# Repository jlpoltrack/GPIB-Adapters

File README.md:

# GPIB-Adapters

GPIB (IEEE-488) adapters that plug straight into an instrument's GPIB socket.

| Folder | What it is |
|---|---|
| [gpib-core](gpib-core) | Shared, board-independent firmware (descended from xyphro's UsbGpib) |
| [LANGPIB-WCH](LANGPIB-WCH) | GPIB to Ethernet/USB on the WCH CH32V407 (on-chip PHY), USB-powered |
| [USBGPIB-STM32](USBGPIB-STM32) | USB to GPIB on an STM32F1: USBTMC and Prologix-compatible serial |

## Build

Clone with `git clone --recurse-submodules`. Each board's firmware builds against `../../gpib-core`.

```
make -C gpib-core test             # host tests
make -C USBGPIB-STM32/Firmware     # arm-none-eabi-gcc
make -C LANGPIB-WCH/Firmware       # riscv-none-elf-gcc (xPack)
```

Flashing and setup are in each board's README and `docs/firmware.md`.

## License

[MIT](LICENSE)

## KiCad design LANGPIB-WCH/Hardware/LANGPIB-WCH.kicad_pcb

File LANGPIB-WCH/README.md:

# LANGPIB-WCH

GPIB-to-Ethernet/USB adapter that plugs onto an instrument's GPIB socket: WCH CH32V407RET6 (on-chip 10/100 PHY), HanRun
HR911105A MagJack (JLC-fitted), USB-C (bus-powered), 4 layers, 57.15 x 46.2 mm, KiCad 10.

`Hardware/` holds the design (schematic PDF, board, renders), `Firmware/` the firmware ([docs/firmware.md](docs/firmware.md)),
`docs/plan.md` the design decisions, `docs/handoff.md` the current state. The schematic, placement and routing are generated by kicad-tools `projects/langpib-wch/`.

**Status (2026-11-21):** 5 assembled boards from JLC ($50.28). Board 1 is brought up and runs an HP 3456A and an HP
66332A over USB (USBTMC, Prologix) and Ethernet (VXI-11, raw SCPI 5025, Prologix 1234, web page); what is still
unverified is listed in [docs/firmware.md](docs/firmware.md) "Still to verify".

## Hardware notes

- **RJ45 (J2):** HanRun HR911105A with magnetics, Bob Smith termination and LEDs inside, through-hole, fitted by JLC.
  MDI pairs are swapped for routing: keep the PHY's Auto-MDIX on.
- **PoE:** use an isolated 802.3af splitter with a USB-C plug, e.g. Adafruit 4552 ([docs/poe.md](docs/poe.md)).
- **GPIB plug (J3) and debug header (J4)** are hand-soldered. J4 (1x7, 2.54 mm): GND, SWIO, SWCLK, NRST, RX, TX, GND,
  the RP2350-Zero probe's order.
- **DFU:** hold SW1 (top left) while plugging in USB for the bootloader (the LQFP-64 has no BOOT pins).
- **Enclosure:** `Enclosure/` (cad-tools `projects/LANGPIB-WCH/`): two snap halves, GPIB plug screws in the bottom; button
  through a flex tab in the lid, status LED through a window in the left wall.
- **Firmware pin map:** DIO1-8 on PB13 / PB15 / PB10 / PB9 / PB12 / PB14 / PB11 / PB8 (one GPIOB read and a 256-entry
  table), REN PA15, EOI PC10, DAV PC11, NRFD PC12, NDAC PD2, IFC PB3, SRQ PB4, ATN PB5 (all 5 V tolerant), DFU PD8,
  status LED PA8, PHY LEDs PD14 (green) / PD15 (yellow) (`AFIO_PCFR1.ETHPHY_LED_RM`), USB PA11 / PA12, SDI PA13 / PA14,
  USART1 PA9 / PA10.

## License

[MIT](../LICENSE)

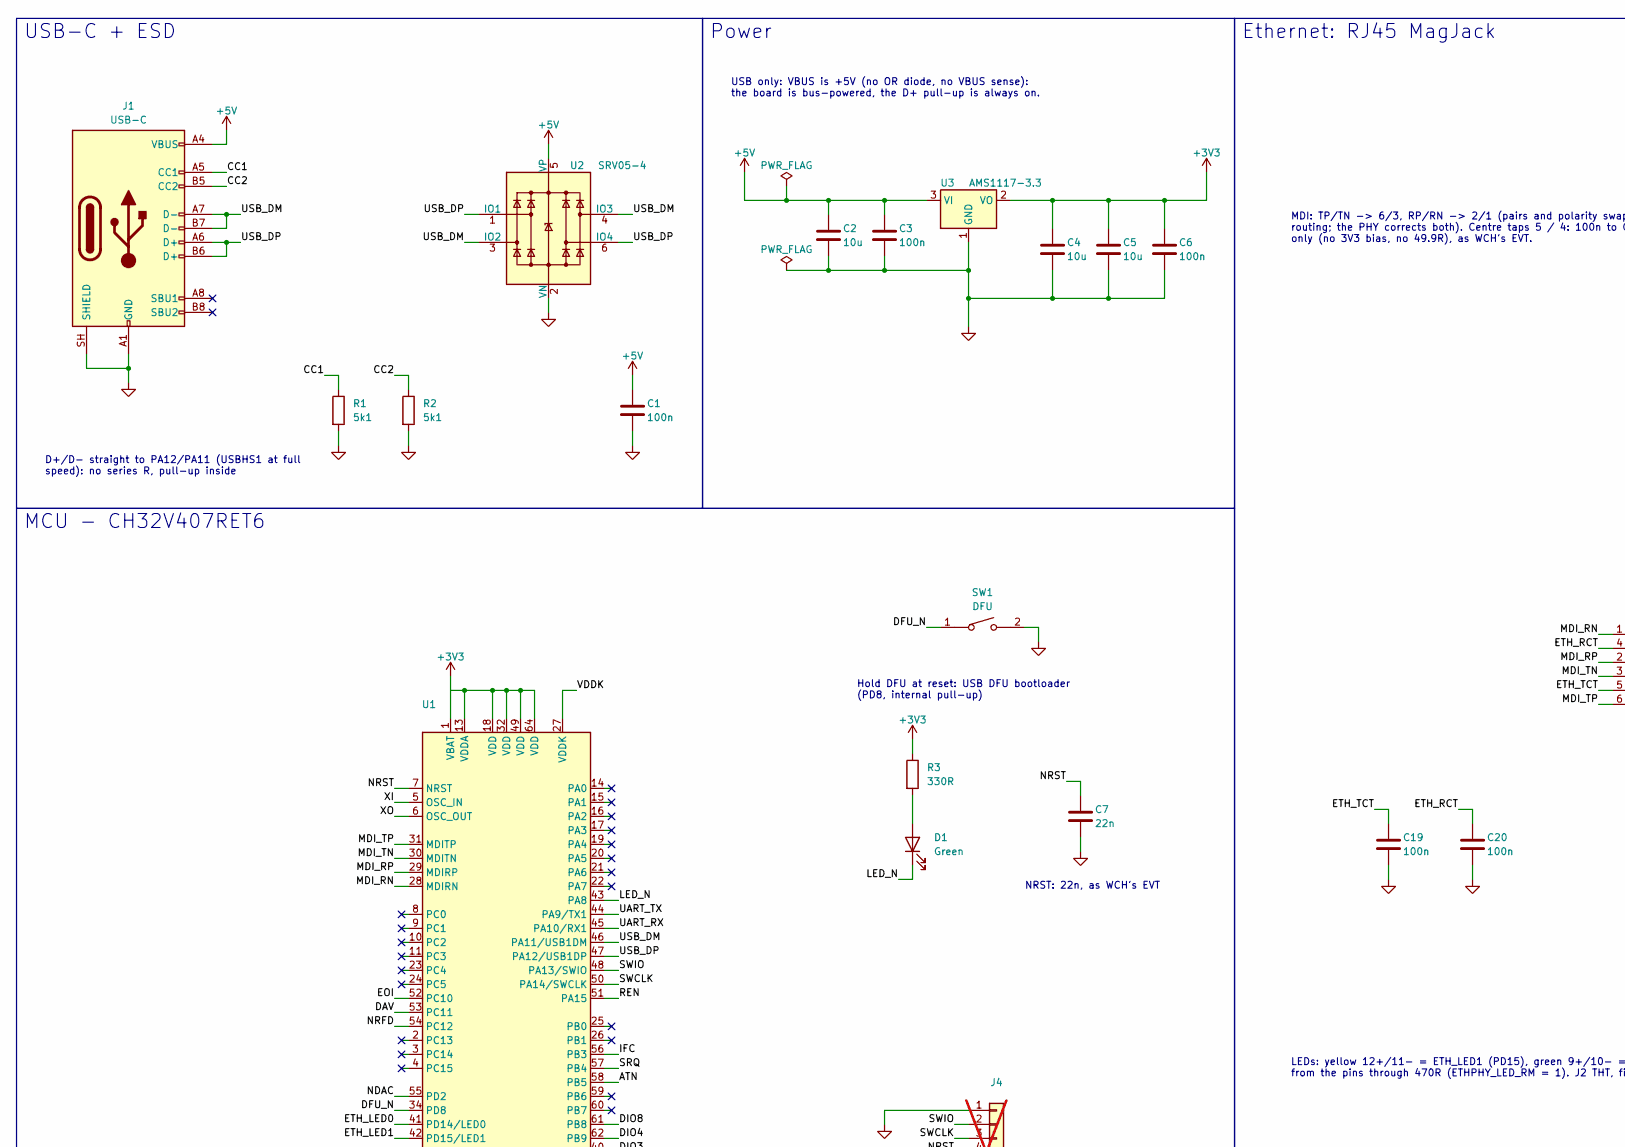
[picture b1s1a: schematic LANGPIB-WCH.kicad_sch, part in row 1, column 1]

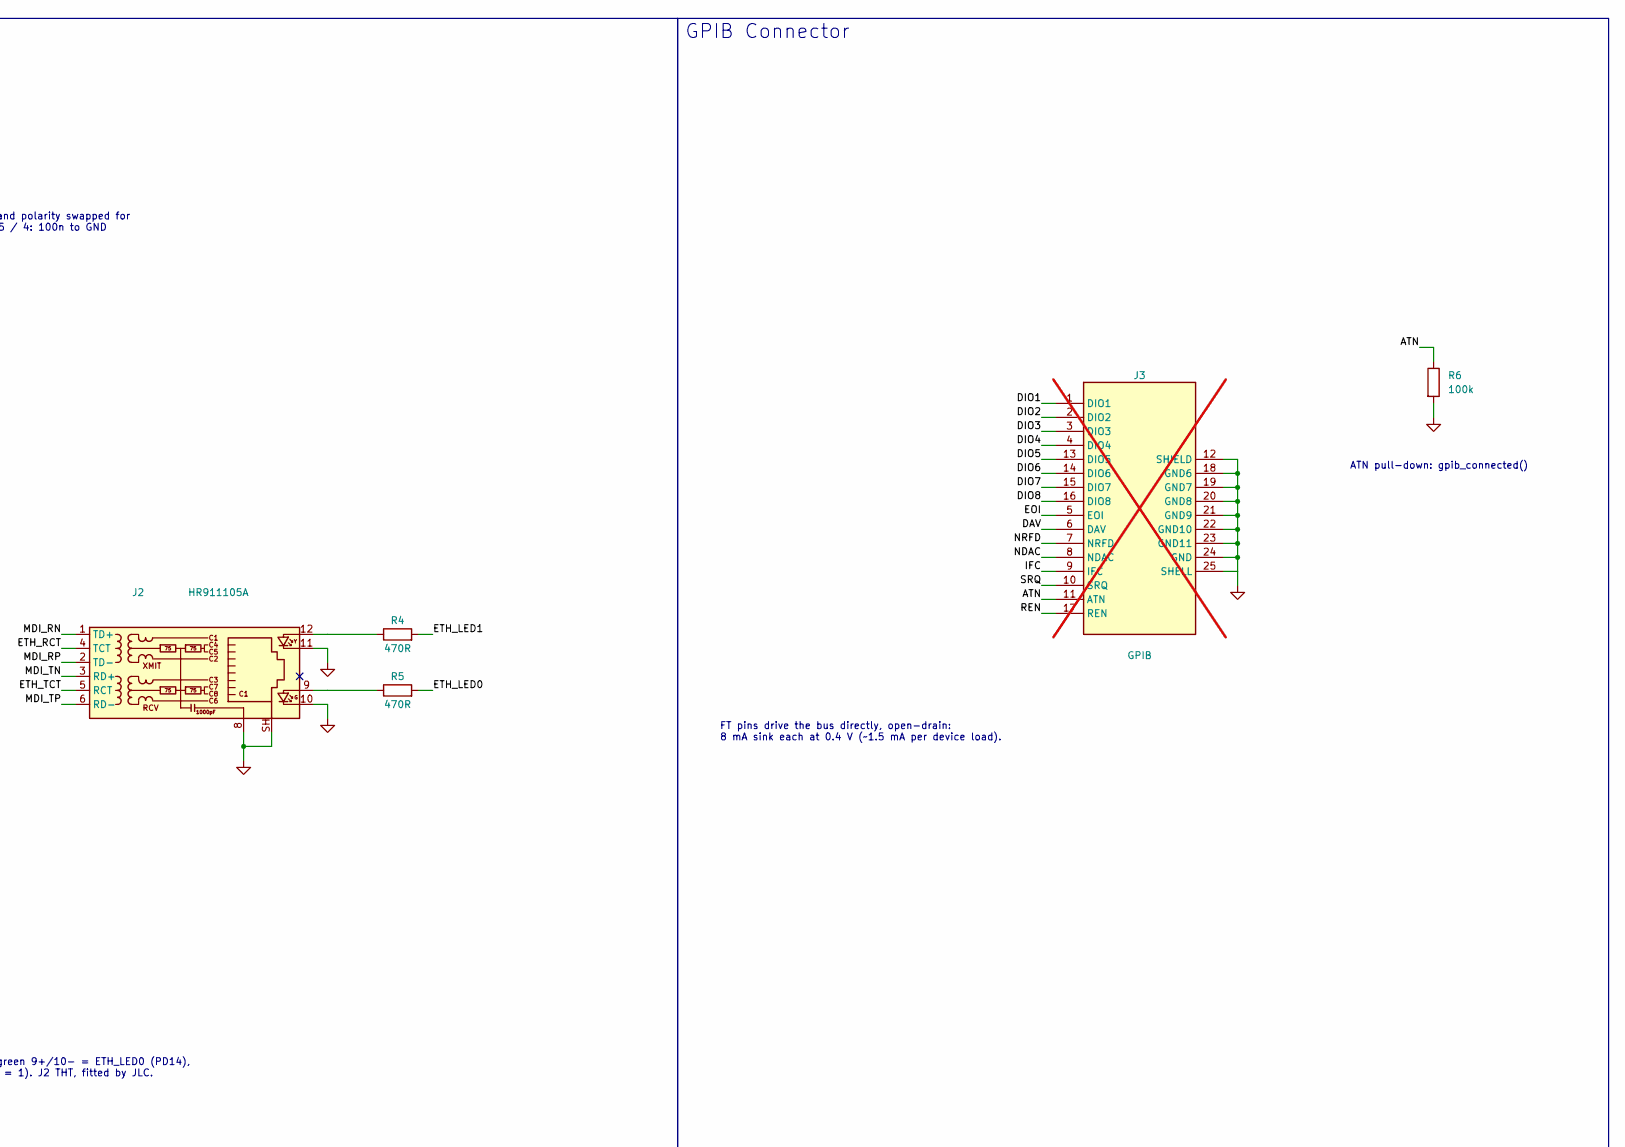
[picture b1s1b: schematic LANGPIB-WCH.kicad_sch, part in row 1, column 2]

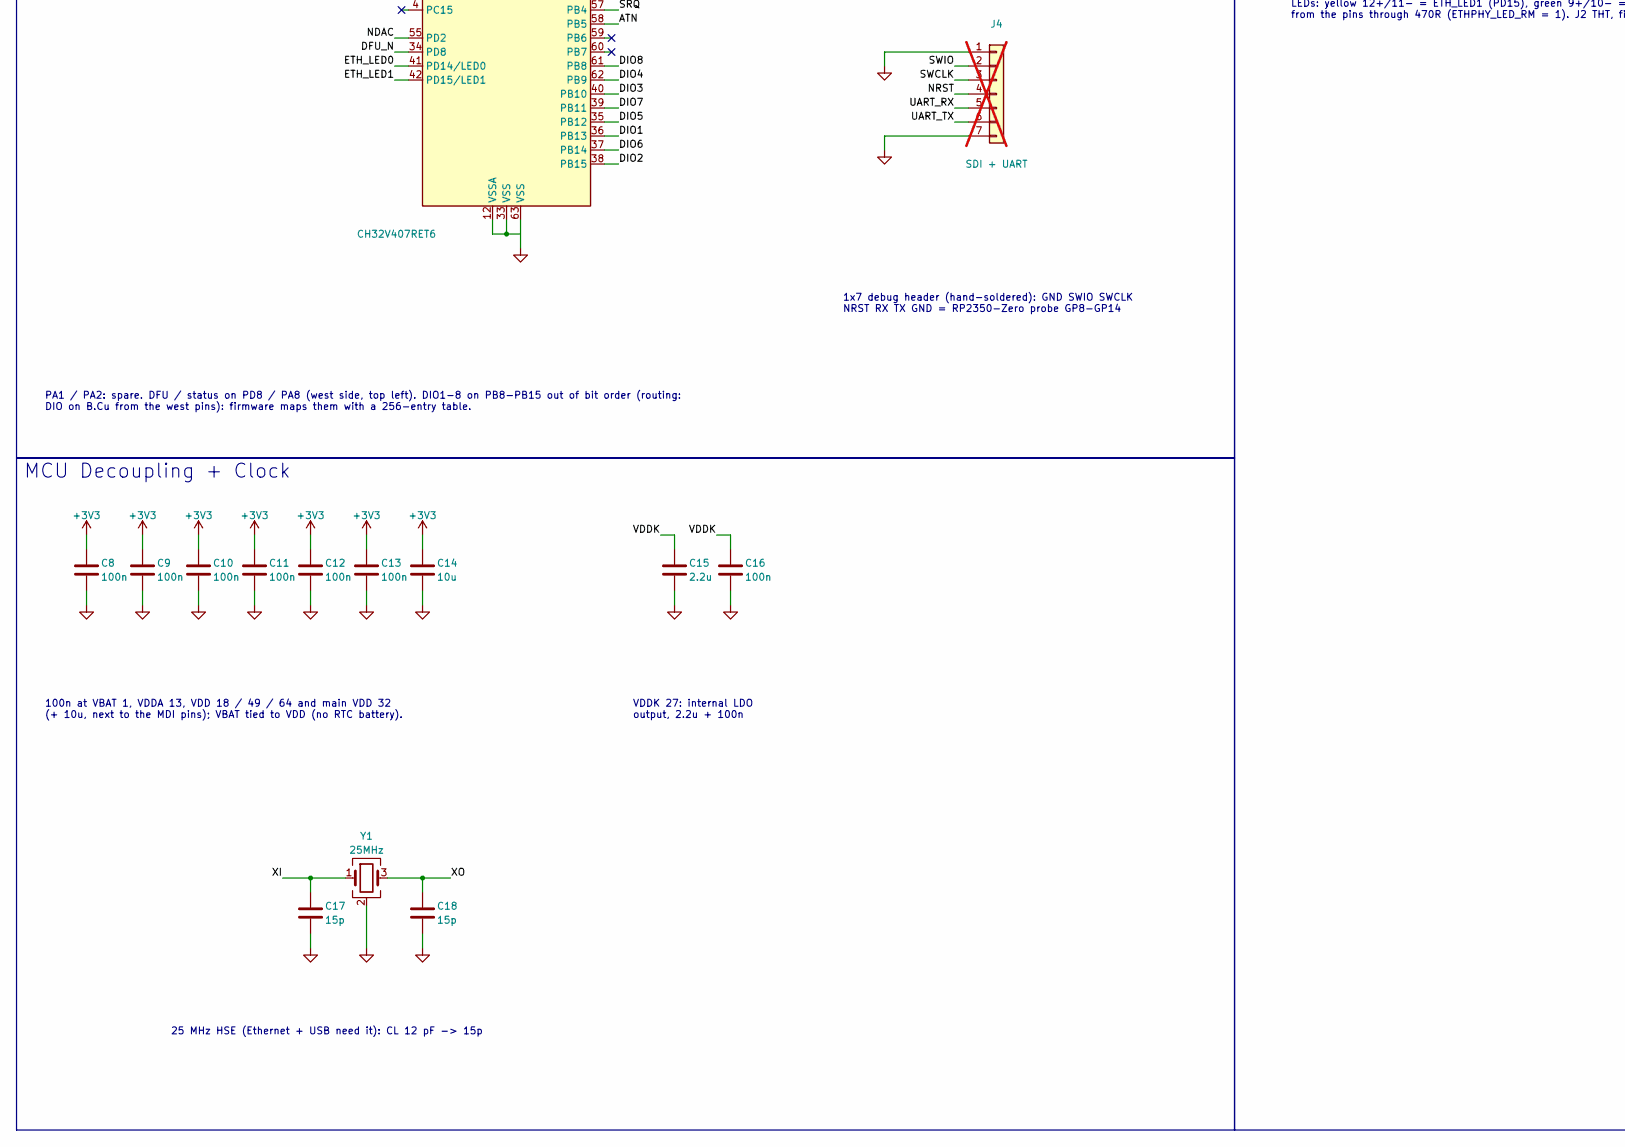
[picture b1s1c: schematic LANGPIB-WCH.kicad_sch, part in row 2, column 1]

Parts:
C1, C3, C6, C8, C9, C10, C11, C12, C13, C16, C19, C20: 100n; C_0402_1005Metric; LCSC C307331
C2, C14: 10u; C_0603_1608Metric; LCSC C96446
C4, C5: 10u; C_0805_2012Metric; LCSC C15850
C7: 22n; C_0402_1005Metric; LCSC C1532
C15: 2.2u; C_0603_1608Metric; LCSC C23630
C17, C18: 15p; C_0402_1005Metric; LCSC C1548
D1: Green; LED_0805_2012Metric_NoSilk; LCSC C2297
J1: USB-C; USB_C_Receptacle_HH_16P_Y495; LCSC C52209111
J2: HR911105A; RJ45_Hanrun_HR911105A_Horizontal; LCSC C12074
J3: GPIB; CONN_112-024-113R001_NRC_NoSilk_GNDRing; not fitted
J4: SDI + UART; PinHeader_1x07_P2.54mm_Vertical; not fitted
R1, R2: 5k1; R_0402_1005Metric; LCSC C25905
R3: 330R; R_0402_1005Metric; LCSC C25104
R4, R5: 470R; R_0402_1005Metric; LCSC C25117
R6: 100k; R_0402_1005Metric; LCSC C25741
SW1: DFU; SW-SMD_L3.9-W3.0-P4.45; MPN TS-1088-AR02016; LCSC C720477
U1: CH32V407RET6; LQFP-64_7x7mm_P0.4mm; LCSC C55068250
U2: SRV05-4; SRV05-4_SOT-23-6; LCSC C85364
U3: AMS1117-3.3; SOT-223-3_TabPin2; LCSC C6186
Y1: 25MHz; Crystal_SMD_3225-4Pin_3.2x2.5mm; LCSC C9006

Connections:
+3V3: C4.1, C5.1, C6.1, C8.1, C9.1, C10.1, C11.1, C12.1, C13.1, C14.1, R3.1, U1.1 (VBAT), U1.13 (VDDA), U1.18 (VDD), U1.32 (VDD), U1.49 (VDD), U1.64 (VDD), U3.2 (VO)
+5V: C1.1, C2.1, C3.1, J1.A4 (VBUS), J1.A9 (VBUS), J1.B4 (VBUS), J1.B9 (VBUS), U2.5 (VP), U3.3 (VI)
/ATN: J3.11 (ATN), R6.1, U1.58 (PB5)
/CC1: J1.A5 (CC1), R1.1
/CC2: J1.B5 (CC2), R2.1
/DAV: J3.6 (DAV), U1.53 (PC11)
/DFU_N: SW1.1, U1.34 (PD8)
/DIO1: J3.1 (DIO1), U1.36 (PB13)
/DIO2: J3.2 (DIO2), U1.38 (PB15)
/DIO3: J3.3 (DIO3), U1.40 (PB10)
/DIO4: J3.4 (DIO4), U1.62 (PB9)
/DIO5: J3.13 (DIO5), U1.35 (PB12)
/DIO6: J3.14 (DIO6), U1.37 (PB14)
/DIO7: J3.15 (DIO7), U1.39 (PB11)
/DIO8: J3.16 (DIO8), U1.61 (PB8)
/EOI: J3.5 (EOI), U1.52 (PC10)
/ETH_LED0: R5.2, U1.41 (PD14/LED0)
/ETH_LED1: R4.2, U1.42 (PD15/LED1)
/ETH_RCT: C20.1, J2.4 (TCT)
/ETH_TCT: C19.1, J2.5 (RCT)
/IFC: J3.9 (IFC), U1.56 (PB3)
/LED_N: D1.1 (K), U1.43 (PA8)
/MDI_RN: J2.1 (TD+), U1.28 (MDIRN)
/MDI_RP: J2.2 (TD-), U1.29 (MDIRP)
/MDI_TN: J2.3 (RD+), U1.30 (MDITN)
/MDI_TP: J2.6 (RD-), U1.31 (MDITP)
/NDAC: J3.8 (NDAC), U1.55 (PD2)
/NRFD: J3.7 (NRFD), U1.54 (PC12)
/NRST: C7.1, J4.4, U1.7 (NRST)
/REN: J3.17 (REN), U1.51 (PA15)
/SRQ: J3.10 (SRQ), U1.57 (PB4)
/SWCLK: J4.3, U1.50 (PA14/SWCLK)
/SWIO: J4.2, U1.48 (PA13/SWIO)
/UART_RX: J4.5, U1.45 (PA10/RX1)
/UART_TX: J4.6, U1.44 (PA9/TX1)
/USB_DM: J1.A7 (D-), J1.B7 (D-), U1.46 (PA11/USB1DM), U2.3 (IO2), U2.4 (IO3)
/USB_DP: J1.A6 (D+), J1.B6 (D+), U1.47 (PA12/USB1DP), U2.1 (IO1), U2.6 (IO4)
/VDDK: C15.1, C16.1, U1.27 (VDDK)
/XI: C17.1, U1.5 (OSC_IN), Y1.1
/XO: C18.1, U1.6 (OSC_OUT), Y1.3
GND: C1.2, C2.2, C3.2, C4.2, C5.2, C6.2, C7.2, C8.2, C9.2, C10.2, C11.2, C12.2, C13.2, C14.2, C15.2, C16.2, C17.2, C18.2, C19.2, C20.2, J1.A1 (GND), J1.A12 (GND), J1.B1 (GND), J1.B12 (GND), J1.SH (SHIELD), J2.8, J2.10, J2.11, J2.SH, J3.12 (SHIELD), J3.18 (GND6), J3.19 (GND7), J3.20 (GND8), J3.21 (GND9), J3.22 (GND10), J3.23 (GND11), J3.24 (GND), J3.25 (SHELL), J4.1, J4.7, R1.2, R2.2, R6.2, SW1.2, U1.12 (VSSA), U1.33 (VSS), U1.63 (VSS), U2.2 (VN), U3.1 (GND), Y1.2 (G), Y1.4 (G)
unnamed: D1.2 (A), R3.2
unnamed: J2.9, R5.1
unnamed: J2.12, R4.1

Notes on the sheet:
USB-C + ESD
Power
MCU - CH32V407RET6
MCU Decoupling + Clock
Ethernet: RJ45 MagJack
GPIB Connector
Notes
DNP = hand-soldered (J3, J4)
D+/D- straight to PA12/PA11 (USBHS1 at full speed): no series R, pull-up inside
USB only: VBUS is +5V (no OR diode, no VBUS sense): the board is bus-powered, the D+ pull-up is always on.
PA1 / PA2: spare. DFU / status on PD8 / PA8 (west side, top left). DIO1-8 on PB8-PB15 out of bit order (routing: DIO on B.Cu from the west pins): firmware maps them with a 256-entry table.
Hold DFU at reset: USB DFU bootloader (PD8, internal pull-up)
NRST: 22n, as WCH's EVT
1x7 debug header (hand-soldered): GND SWIO SWCLK NRST RX TX GND = RP2350-Zero probe GP8-GP14
100n at VBAT 1, VDDA 13, VDD 18 / 49 / 64 and main VDD 32 (+ 10u, next to the MDI pins); VBAT tied to VDD (no RTC battery).
VDDK 27: internal LDO output, 2.2u + 100n
25 MHz HSE (Ethernet + USB need it): CL 12 pF -> 15p
MDI: TP/TN -> 6/3, RP/RN -> 2/1 (pairs and polarity swapped for routing; the PHY corrects both). Centre taps 5 / 4: 100n to GND only (no 3V3 bias, no 49.9R), as WCH's EVT.
LEDs: yellow 12+/11- = ETH_LED1 (PD15), green 9+/10- = ETH_LED0 (PD14), from the pins through 470R (ETHPHY_LED_RM = 1). J2 THT, fitted by JLC.
ATN pull-down: gpib_connected()
FT pins drive the bus directly, open-drain: 8 mA sink each at 0.4 V (~1.5 mA per device load).

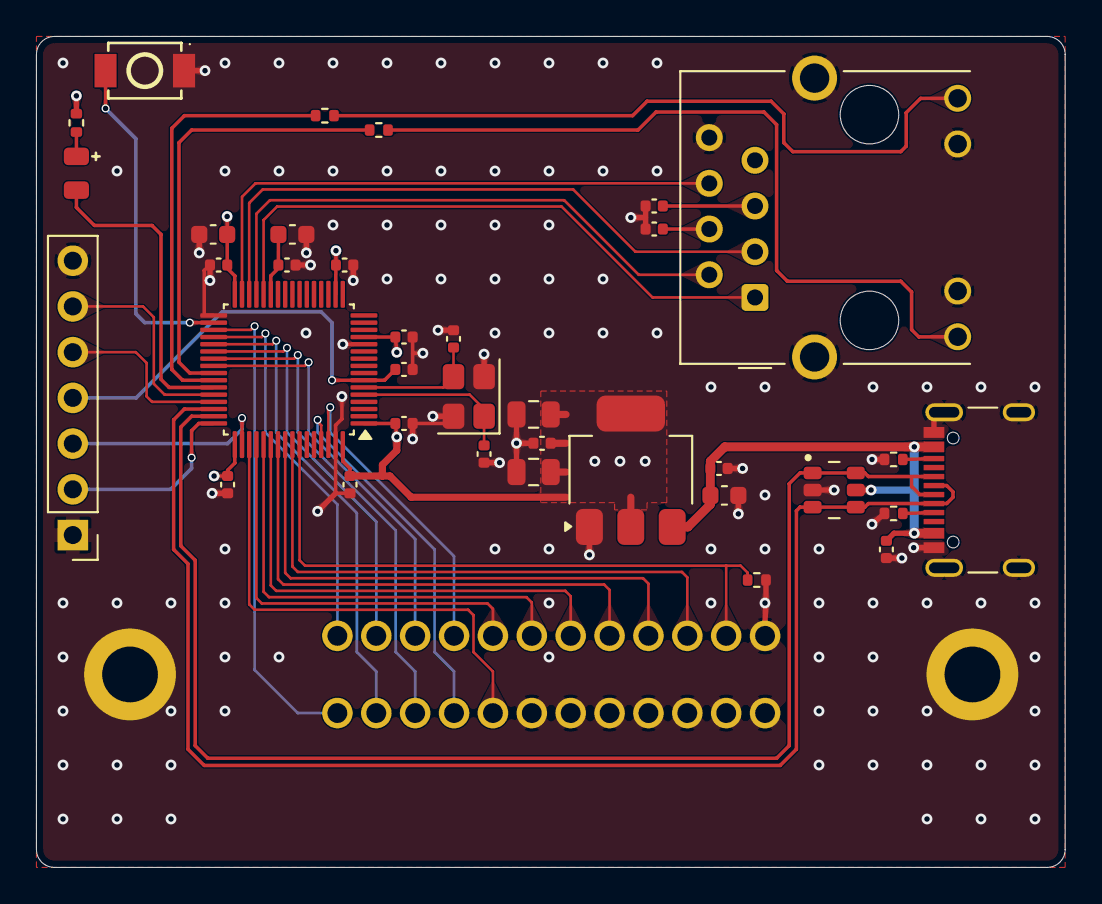
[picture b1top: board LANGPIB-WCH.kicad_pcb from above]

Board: 4 copper layers, 57.2 x 46.2 mm, 37 parts (0 on the bottom side), 44 nets.

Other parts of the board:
LOGO1: title

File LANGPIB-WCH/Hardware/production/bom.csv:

Designator,Footprint,Quantity,Value,LCSC Part #
"C1, C10, C11, C12, C13, C16, C19, C20, C3, C6, C8, C9",0402,12,100n,C307331
"C14, C2",0603,2,10u,C96446
C15,0603,1,2.2u,C23630
"C17, C18",0402,2,15p,C1548
"C4, C5",0805,2,10u,C15850
C7,0402,1,22n,C1532
D1,0805,1,Green,C2297
J1,USB_C_Receptacle_HH_16P_Y495,1,USB-C,C52209111
J2,RJ45_Hanrun_HR911105A_Horizontal,1,HR911105A,C12074
"R1, R2",0402,2,5k1,C25905
R3,0402,1,330R,C25104
"R4, R5",0402,2,470R,C25117
R6,0402,1,100k,C25741
SW1,SW-SMD_L3.9-W3.0-P4.45,1,DFU,C720477
U1,LQFP-64_7x7mm_P0.4mm,1,CH32V407RET6,C55068250
U2,SRV05-4_SOT-23-6,1,SRV05-4,C85364
U3,SOT-223-3_TabPin2,1,AMS1117-3.3,C6186
Y1,Crystal_SMD_3225-4Pin_3.2x2.5mm,1,25MHz,C9006

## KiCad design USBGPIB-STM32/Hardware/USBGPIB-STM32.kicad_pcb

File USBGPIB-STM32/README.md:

# USBGPIB-STM32

A USB to GPIB (IEEE-488) adapter: an STM32F1 port of [xyphro's UsbGpib](https://github.com/xyphro/UsbGpib). It plugs straight into an instrument's GPIB socket and shows up as a USBTMC device for VISA and as a Prologix-compatible serial port.

Designed in KiCad 10.

## Status

Prototype. A V1.0 board works on macOS with an HP 3456A (USBTMC and Prologix) and an HP 66332A (PyVISA). Not tested yet: Windows, Linux, NI or Keysight VISA, several instruments on one bus, bus timing on a logic analyser, the web app, the enclosure, and V1.1 boards.

The firmware uses the pid.codes test ID 1209:0001, which must be replaced before release.

## Features

- STM32F103C8T6 at 72 MHz from a 16 MHz crystal; USB 2.0 full speed (TinyUSB).
- Composite USB device: USBTMC/USB488, a serial port speaking the Prologix `++` protocol, and DFU.
- GPIB lines driven directly from the MCU's 5 V-tolerant pins in open-drain mode, no bus drivers: fine for about 5 instruments on the bus.
- USB-C with 5K1 CC pull-downs, SRV05-4 ESD protection, XC6206 3.3 V LDO.
- DFU bootloader (dapboot), entered from USB or by holding SW1 while plugging in; SWD and UART headers.
- Browser app (`web/`, Chrome or Edge): settings, bus scan, terminal, plotter capture and firmware updates.

## Connectors

| Ref | Part | Pins |
|---|---|---|
| J1 | USB-C receptacle | USB 2.0 (D+/D−), VBUS, CC1/CC2 5K1 to GND |
| J2 | Norcomp 112-024-113R001, 24-pin GPIB plug, right angle | IEEE-488 pinout; DNP, soldered by hand |
| J3 | 1×3 header, UART2 | 1 GND, 2 TX (PA2), 3 RX (PA3); 3.3 V only; DNP |
| J4 | 1×4 header, SWD | V1.1: 1 GND, 2 SWCLK, 3 SWDIO, 4 NRST. V1.0: 1 SWDIO, 2 SWCLK, 3 GND. No power; DNP |

SW1 is the DFU button (PA1 to GND): it only counts when held while plugging in; a press while running does nothing.
D2 is the status LED (PC13).

## GPIB pin map

| Signal | GPIB pin | STM32 | | Signal | GPIB pin | STM32 |
|---|---|---|---|---|---|---|
| DIO1 | 1 | PB9 | | EOI | 5 | PB12 |
| DIO2 | 2 | PB7 | | DAV | 6 | PB13 |
| DIO3 | 3 | PB10 | | NRFD | 7 | PB14 |
| DIO4 | 4 | PB11 | | NDAC | 8 | PB15 |
| DIO5 | 13 | PB8 | | IFC | 9 | PA8 |
| DIO6 | 14 | PB6 | | SRQ | 10 | PA9 |
| DIO7 | 15 | PB4 | | ATN | 11 | PA10 |
| DIO8 | 16 | PB3 | | REN | 17 | PA15 |

GND on GPIB pins 12 and 18–24.

## Build

You need `make`, the [Arm GNU toolchain](https://developer.arm.com/downloads/-/arm-gnu-toolchain-downloads) and Node 22 (for the web app).

- macOS: `brew install --cask gcc-arm-embedded`
- Debian or Ubuntu: `sudo apt install build-essential gcc-arm-none-eabi libnewlib-arm-none-eabi`

```sh
git clone --recurse-submodules https://github.com/jlpoltrack/GPIB-Adapters.git
cd USBGPIB-STM32

make -C Firmware              # Firmware/build/usbgpib.bin
make -C Firmware bootloader   # bootloader/dapboot/src/dapboot.bin
make -C Firmware test         # host tests

cd web && npm ci && npm test && npm run build   # web/dist; npm run dev serves it locally
```

## Flash

The first flash goes over SWD (J4, ST-Link, [pyOCD](https://pyocd.io)). Later updates go over USB ([dfu-util](https://dfu-util.sourceforge.net)).

```sh
make -C Firmware flash-all    # first time: dapboot and the app
make -C Firmware dfu          # later: the running app restarts into dapboot
```

`dfu-util` may end with `unable to read DFU status` (exit 74): that is harmless, dapboot resets as it finishes.
The app embeds dapboot and rewrites it at boot when it differs, so a USB update of the app updates the bootloader too.

Without dfu-util: open <https://jlpoltrack.github.io/GPIB-Adapters/> in Chrome or Edge, click Update firmware and
pick the adapter. The page also updates LANGPIB-WCH; it finds which adapter is plugged in and writes the latest
release. Without an instrument on the bus, hold SW1 while plugging in first.

Releases: push a tag `vX.Y` on main. The workflow (`.github/workflows/pages.yml`) builds and tests both firmwares,
creates the GitHub Release with `USBGPIB-STM32-vX.Y.bin` and `LANGPIB-WCH-vX.Y.dfu`, and deploys the web page with
those files (when the repo variable `PAGES_ENABLED` is `true`). Pushes and PRs only build and test.

## Use

The adapter only appears on USB once it has found an instrument, and the USBTMC side binds to that instrument. The serial port reaches any address on the bus, e.g. `++addr 5`, then `*IDN?` and `++read eoi`. Without an instrument the LED blinks; hold SW1 while plugging in to reach dapboot.

Commands and internals: [docs/firmware.md](docs/firmware.md). Design notes: [docs/hardware.md](docs/hardware.md).

## Bill of materials

All assembled parts have LCSC numbers: [Hardware/production/bom.csv](Hardware/production/bom.csv). J2 is hand-soldered.

## Files

| Path | What |
|---|---|
| `Hardware/` | KiCad project, schematic PDF, renders; `KiCADv6/` holds the J2 symbol |
| `Hardware/production/` | generated with the [Fabrication Toolkit](https://github.com/bennymeg/Fabrication-Toolkit) plugin, ready for JLCPCB |
| `Enclosure/` | 3D-printed snap-fit case: 3MF to print, STEP for CAD |
| `Firmware/` | application firmware; shared code is in [gpib-core](../gpib-core) |
| `bootloader/dapboot/` | DFU bootloader (submodule) |
| `web/` | Web Serial / WebUSB browser app |
| `tools/` | board checks and instrument tests, below |

Tool setup: `python3 -m venv .venv`, `.venv/bin/pip install -r tools/requirements.txt`. Tools that use SWD run under pyOCD's Python.

| Tool | What |
|---|---|
| `flash_board.py` | first flash of a new board, read back and checked |
| `gpib_shorts.py` | solder-bridge test of the GPIB lines over SWD |
| `bringup.py`, `swd_rescue.py` | SWD tests on the bring-up image (`make -C Firmware flash-bringup`); recovering a board with no NRST wired |
| `usb_bench.py` | USB checks on the no-instrument image (`make -C Firmware BENCH=1 flash`) |
| `hp3456a_check.py`, `hp66332a_check.py` | end-to-end tests against those instruments |
| `bench_throughput.py` | USBTMC read throughput |
| `latency_3456a.py` | per-transfer timing of one HP 3456A reading, display on vs off, USBTMC and Prologix. Found that the meter's display refresh, not the adapter, costs ~130 ms per reading |

## License

[MIT](../LICENSE). Firmware derived from UsbGpib by Kai Gossner (MIT).

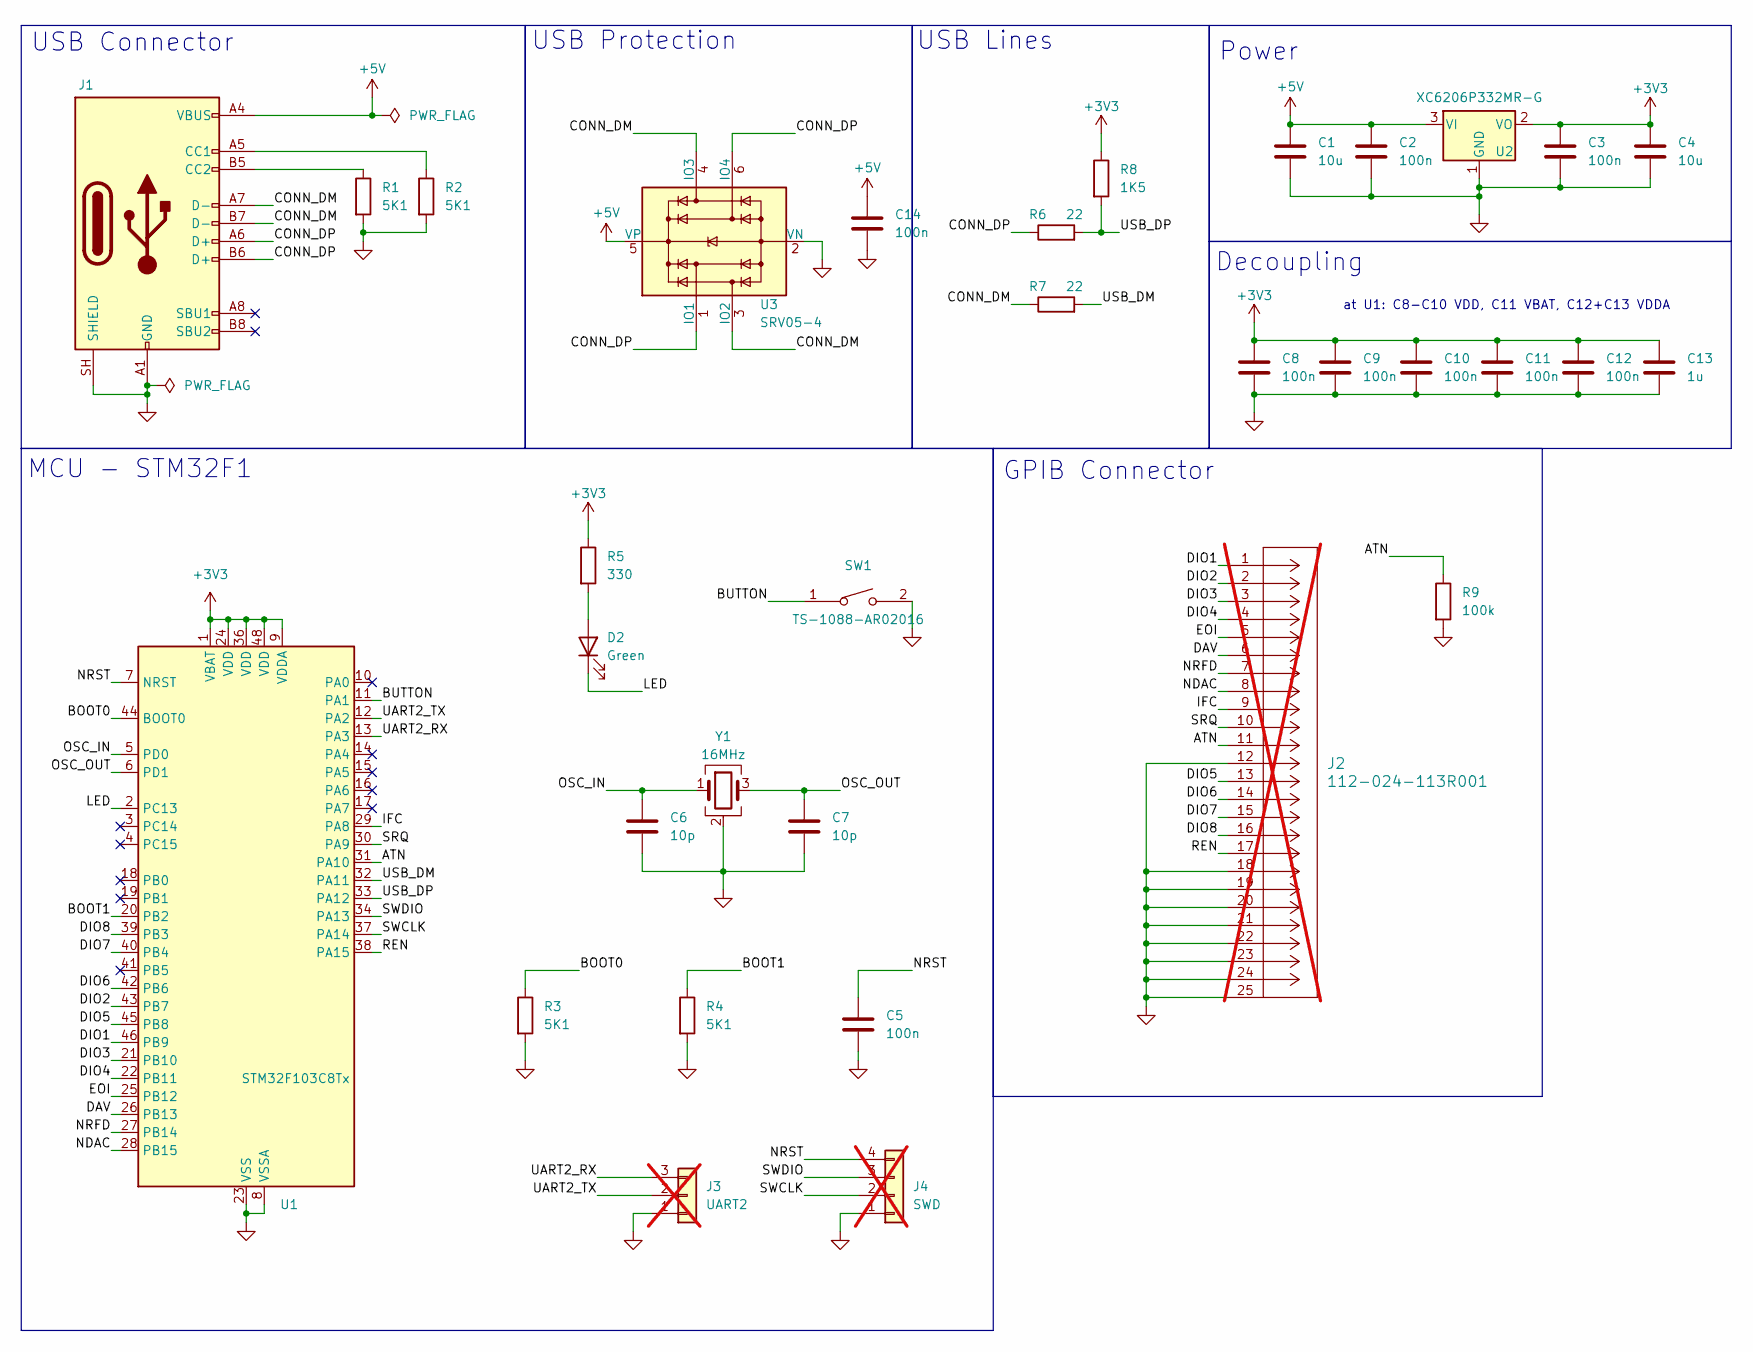
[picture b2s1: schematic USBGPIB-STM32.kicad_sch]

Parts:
C1, C4: 10u; C_0603_1608Metric; LCSC C96446
C2: 100n; C_0402_1005Metric; LCSC C307331
C3, C5, C8, C9, C10, C11, C12, C14: 100n; C_0402_1005Metric; LCSC C1525
C6, C7: 10p; C_0402_1005Metric; LCSC C32949
C13: 1u; C_0402_1005Metric; LCSC C52923
D2: Green; LED_0805_2012Metric_NoSilk; LCSC C2297
J1: USB_C_Receptacle_USB2.0_16P; USB_C_Receptacle_HH_16P_Y495; LCSC C52209111
J2: 112-024-113R001; CONN_112-024-113R001_NRC_NoSilk_GNDRing; not fitted
J3: UART2; PinHeader_1x03_P2.54mm_Vertical; LCSC C49257; not fitted
J4: SWD; PinHeader_1x04_P2.54mm_Vertical; LCSC C32713270; not fitted
R1, R2, R3, R4: 5K1; R_0402_1005Metric; LCSC C25905
R5: 330; R_0402_1005Metric; LCSC C25104
R6, R7: 22; R_0402_1005Metric; LCSC C25092
R8: 1K5; R_0402_1005Metric; LCSC C25867
R9: 100k; R_0402_1005Metric; LCSC C25741
SW1: TS-1088-AR02016; SW-SMD_L3.9-W3.0-P4.45; LCSC C720477
U1: STM32F103C8Tx; LQFP-48_7x7mm_P0.5mm; LCSC C8734
U2: XC6206P332MR-G; SOT-23-3; LCSC C5446
U3: SRV05-4; SRV05-4_SOT-23-6; LCSC C85364
Y1: 16MHz; Crystal_SMD_3225-4Pin_3.2x2.5mm; LCSC C13738

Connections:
+3V3: C3.1, C4.1, C8.1, C9.1, C10.1, C11.1, C12.1, C13.1, R5.1, R8.1, U1.1 (VBAT), U1.9 (VDDA), U1.24 (VDD), U1.36 (VDD), U1.48 (VDD), U2.2 (VO)
+5V: C1.1, C2.1, C14.1, J1.A4 (VBUS), J1.A9 (VBUS), J1.B4 (VBUS), J1.B9 (VBUS), U2.3 (VI), U3.5 (VP)
/ATN: J2.11, R9.1, U1.31 (PA10)
/BOOT0: R3.1, U1.44 (BOOT0)
/BOOT1: R4.1, U1.20 (PB2)
/BUTTON: SW1.1, U1.11 (PA1)
/CONN_DM: J1.A7 (D-), J1.B7 (D-), R7.1, U3.3 (IO2), U3.4 (IO3)
/CONN_DP: J1.A6 (D+), J1.B6 (D+), R6.1, U3.1 (IO1), U3.6 (IO4)
/DAV: J2.6, U1.26 (PB13)
/DIO1: J2.1, U1.46 (PB9)
/DIO2: J2.2, U1.43 (PB7)
/DIO3: J2.3, U1.21 (PB10)
/DIO4: J2.4, U1.22 (PB11)
/DIO5: J2.13, U1.45 (PB8)
/DIO6: J2.14, U1.42 (PB6)
/DIO7: J2.15, U1.40 (PB4)
/DIO8: J2.16, U1.39 (PB3)
/EOI: J2.5, U1.25 (PB12)
/IFC: J2.9, U1.29 (PA8)
/LED: D2.1 (K), U1.2 (PC13)
/NDAC: J2.8, U1.28 (PB15)
/NRFD: J2.7, U1.27 (PB14)
/NRST: C5.1, J4.4, U1.7 (NRST)
/OSC_IN: C6.1, U1.5 (PD0), Y1.1
/OSC_OUT: C7.1, U1.6 (PD1), Y1.3
/REN: J2.17, U1.38 (PA15)
/SRQ: J2.10, U1.30 (PA9)
/SWCLK: J4.2, U1.37 (PA14)
/SWDIO: J4.3, U1.34 (PA13)
/UART2_RX: J3.3, U1.13 (PA3)
/UART2_TX: J3.2, U1.12 (PA2)
/USB_DM: R7.2, U1.32 (PA11)
/USB_DP: R6.2, R8.2, U1.33 (PA12)
GND: C1.2, C2.2, C3.2, C4.2, C5.2, C6.2, C7.2, C8.2, C9.2, C10.2, C11.2, C12.2, C13.2, C14.2, J1.A1 (GND), J1.A12 (GND), J1.B1 (GND), J1.B12 (GND), J1.SH (SHIELD), J2.12, J2.18, J2.19, J2.20, J2.21, J2.22, J2.23, J2.24, J2.25 (SHELL), J3.1, J4.1, R1.2, R2.2, R3.2, R4.2, R9.2, SW1.2, U1.8 (VSSA), U1.23 (VSS), U1.35 (VSS), U1.47 (VSS), U2.1 (GND), U3.2 (VN), Y1.2 (G), Y1.4 (G)
unnamed: D2.2 (A), R5.2
unnamed: J1.A5 (CC1), R2.1
unnamed: J1.B5 (CC2), R1.1

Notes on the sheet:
MCU - STM32F1
Decoupling
Power
at U1: C8-C10 VDD, C11 VBAT, C12+C13 VDDA
USB Protection
GPIB Connector
USB Connector
USB Lines

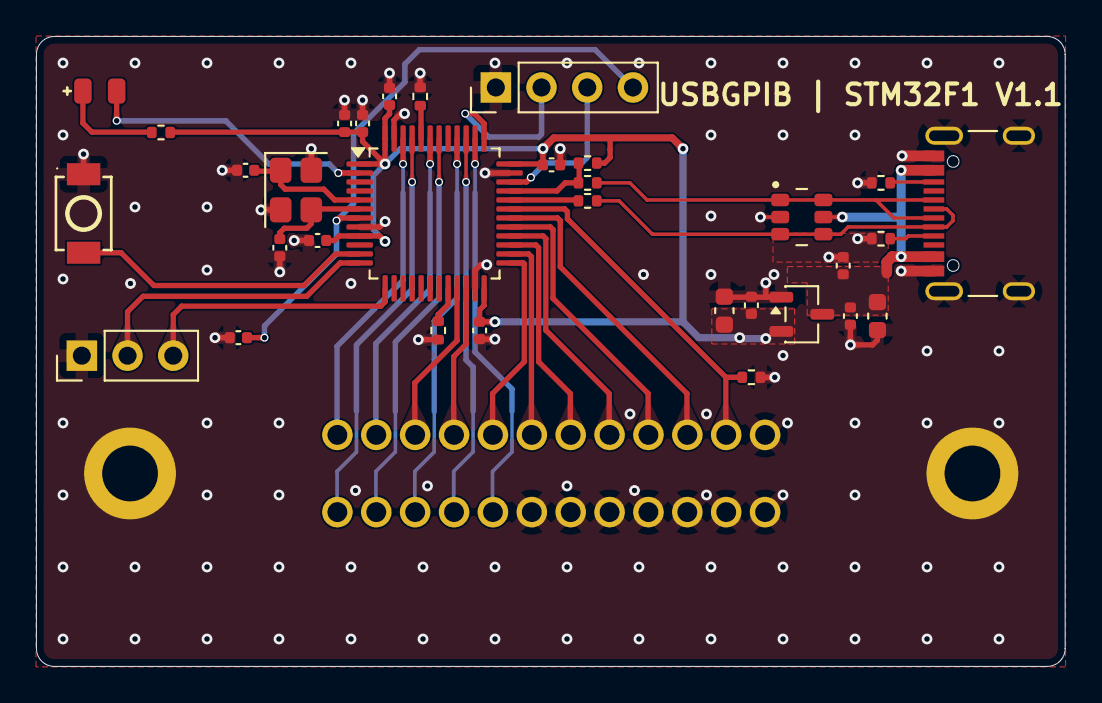
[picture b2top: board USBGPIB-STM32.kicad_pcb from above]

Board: 2 copper layers, 57.1 x 35.0 mm, 35 parts (0 on the bottom side), 37 nets.

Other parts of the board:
LOGO1, LOGO2: title

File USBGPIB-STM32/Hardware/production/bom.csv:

Designator,Footprint,Quantity,Value,LCSC Part #
"C1, C4",0603,2,10u,C96446
"C10, C11, C12, C14, C3, C5, C8, C9",0402,8,100n,C1525
C13,0402,1,1u,C52923
C2,0402,1,100n,C307331
"C6, C7",0402,2,10p,C32949
D2,0805,1,Green,C2297
J1,USB_C_Receptacle_HH_16P_Y495,1,USB_C_Receptacle_USB2.0_16P,C52209111
"R1, R2, R3, R4",0402,4,5K1,C25905
R5,0402,1,330,C25104
"R6, R7",0402,2,22,C25092
R8,0402,1,1K5,C25867
R9,0402,1,100k,C25741
SW1,SW-SMD_L3.9-W3.0-P4.45,1,TS-1088-AR02016,C720477
U1,LQFP-48_7x7mm_P0.5mm,1,STM32F103C8Tx,C8734
U2,SOT-23-3,1,XC6206P332MR-G,C5446
U3,SRV05-4_SOT-23-6,1,SRV05-4,C85364
Y1,Crystal_SMD_3225-4Pin_3.2x2.5mm,1,16MHz,C13738

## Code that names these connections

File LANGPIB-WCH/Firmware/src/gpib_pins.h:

#ifndef GPIB_PINS_H_
#define GPIB_PINS_H_

/* GPIB line access for gpib_phy.c. Every line is an FT pin in open-drain output mode: OUTDR=0 drives low, 1 releases
 * (SRQ is a floating input). Controls are spread over four ports; DIO1-8 sit on PB8-PB15 out of bit order (routing),
 * so data goes through two 256-entry tables (docs/plan.md, GPIB pin map). */

#include "ch32v4x7.h"

#define REN_PORT  GPIOA
#define REN_PIN   15
#define EOI_PORT  GPIOC
#define EOI_PIN   10
#define DAV_PORT  GPIOC
#define DAV_PIN   11
#define NRFD_PORT GPIOC
#define NRFD_PIN  12
#define NDAC_PORT GPIOD
#define NDAC_PIN  2
#define IFC_PORT  GPIOB
#define IFC_PIN   3
#define SRQ_PORT  GPIOB
#define SRQ_PIN   4  /* input only */
#define ATN_PORT  GPIOB
#define ATN_PIN   5  /* R6 100k pull-down: reads low with no bus (gpib_connected()) */

#define DATA_PORT  GPIOB
#define DATA_SHIFT 8 /* DIO on PB8-PB15 */
#define DATA_MASK  (0xFFu << DATA_SHIFT)

/* DIOn -> PB bit - 8: DIO1 PB13, DIO2 PB15, DIO3 PB10, DIO4 PB9, DIO5 PB12, DIO6 PB14, DIO7 PB11, DIO8 PB8 */
#define DIO_TO_PORT(d) ((((d) >> 0 & 1u) << 5) | (((d) >> 1 & 1u) << 7) | (((d) >> 2 & 1u) << 2) | \
                        (((d) >> 3 & 1u) << 1) | (((d) >> 4 & 1u) << 4) | (((d) >> 5 & 1u) << 6) | \
                        (((d) >> 6 & 1u) << 3) | (((d) >> 7 & 1u) << 0))
#define PORT_TO_DIO(p) ((((p) >> 5 & 1u) << 0) | (((p) >> 7 & 1u) << 1) | (((p) >> 2 & 1u) << 2) | \
                        (((p) >> 1 & 1u) << 3) | (((p) >> 4 & 1u) << 4) | (((p) >> 6 & 1u) << 5) | \
                        (((p) >> 3 & 1u) << 6) | (((p) >> 0 & 1u) << 7))

#ifdef GPIB_SIM
#include "gpib_sim_pins.h" /* SIM=1: gpib-core's simulated bus; the GPIB pins stay as reset left them */
#else

#define LINE_LOW(l)   (l##_PORT->BCR = 1u << l##_PIN)
#define LINE_HIGH(l)  (l##_PORT->BSHR = 1u << l##_PIN)
#define LINE_STATE(l) (l##_PORT->INDR & (1u << l##_PIN))
#define LINE_OUT(l)   (l##_PORT->OUTDR & (1u << l##_PIN))

#define ATN_LOW   LINE_LOW(ATN)
#define ATN_HIGH  LINE_HIGH(ATN)
#define NDAC_LOW  LINE_LOW(NDAC)
#define NDAC_HIGH LINE_HIGH(NDAC)
#define NRFD_LOW  LINE_LOW(NRFD)
#define NRFD_HIGH LINE_HIGH(NRFD)
#define DAV_LOW   LINE_LOW(DAV)
#define DAV_HIGH  LINE_HIGH(DAV)
#define EOI_LOW   LINE_LOW(EOI)
#define EOI_HIGH  LINE_HIGH(EOI)
#define REN_LOW   LINE_LOW(REN)
#define REN_HIGH  LINE_HIGH(REN)
#define IFC_LOW   LINE_LOW(IFC)
#define IFC_HIGH  LINE_HIGH(IFC)

#define DAV_STATE  LINE_STATE(DAV)
#define NDAC_STATE LINE_STATE(NDAC)
#define NRFD_STATE LINE_STATE(NRFD)
#define ATN_STATE  LINE_STATE(ATN)
#define EOI_STATE  LINE_STATE(EOI)
#define SRQ_STATE  LINE_STATE(SRQ)

/* true when ATN is released */
#define ATN_OUT_STATE (LINE_OUT(ATN) != 0)

#define GPIB_T4(M, i)   M(i), M((i) + 1), M((i) + 2), M((i) + 3)
#define GPIB_T16(M, i)  GPIB_T4(M, i), GPIB_T4(M, (i) + 4), GPIB_T4(M, (i) + 8), GPIB_T4(M, (i) + 12)
#define GPIB_T64(M, i)  GPIB_T16(M, i), GPIB_T16(M, (i) + 16), GPIB_T16(M, (i) + 32), GPIB_T16(M, (i) + 48)
#define GPIB_T256(M)    GPIB_T64(M, 0), GPIB_T64(M, 64), GPIB_T64(M, 128), GPIB_T64(M, 192)

static const uint8_t s_dio_to_port[256] = { GPIB_T256(DIO_TO_PORT) };
static const uint8_t s_port_to_dio[256] = { GPIB_T256(PORT_TO_DIO) };

/* GPIB data is negative logic: a 1 bit pulls the line low. One BSHR write: reset the 1s, set the 0s. */
#define DATA_WRITE(d) (DATA_PORT->BSHR = ((uint32_t)s_dio_to_port[(uint8_t)(d)] << (DATA_SHIFT + 16)) | \
                                         ((uint32_t)(uint8_t)~s_dio_to_port[(uint8_t)(d)] << DATA_SHIFT))
#define DATA_RELEASE  (DATA_PORT->BSHR = DATA_MASK)
#define DATA_READ     (s_port_to_dio[(uint8_t)~(DATA_PORT->INDR >> DATA_SHIFT)])

/* 4-bit CFGxR field: 0x6 open-drain output 2 MHz (the slowest edges: HS pins, a cable), 0x4 floating input */
#define GPIB_OD 0x6u

static inline void gpib_pin_cfg(GPIO_TypeDef *port, unsigned pin, uint32_t mode)
{
	volatile uint32_t *cfg = (pin < 8) ? &port->CFGLR : &port->CFGHR;
	unsigned sh = (pin & 7u) * 4u;
	*cfg = (*cfg & ~(0xFu << sh)) | (mode << sh);
}

/* Everything starts released; REN keeps its output level (low from reset), phy_init() then sets it. No pulls: the
 * bus has 5 V terminations, and ATN needs R6 alone to read low with no bus. */
static inline void gpib_pins_init(void)
{
	RCC->PB2PCENR |= RCC_IOPAEN | RCC_IOPBEN | RCC_IOPCEN | RCC_IOPDEN;

	DATA_RELEASE;
	EOI_HIGH;
	DAV_HIGH;
	NRFD_HIGH;
	NDAC_HIGH;
	IFC_HIGH;
	ATN_HIGH;
	for (unsigned pin = 8; pin < 16; pin++)
		gpib_pin_cfg(DATA_PORT, pin, GPIB_OD);
	gpib_pin_cfg(REN_PORT, REN_PIN, GPIB_OD);
	gpib_pin_cfg(EOI_PORT, EOI_PIN, GPIB_OD);
	gpib_pin_cfg(DAV_PORT, DAV_PIN, GPIB_OD);
	gpib_pin_cfg(NRFD_PORT, NRFD_PIN, GPIB_OD);
	gpib_pin_cfg(NDAC_PORT, NDAC_PIN, GPIB_OD);
	gpib_pin_cfg(IFC_PORT, IFC_PIN, GPIB_OD);
	gpib_pin_cfg(ATN_PORT, ATN_PIN, GPIB_OD);
	gpib_pin_cfg(SRQ_PORT, SRQ_PIN, 0x4u);
}

#endif /* GPIB_SIM */
#endif /* GPIB_PINS_H_ */

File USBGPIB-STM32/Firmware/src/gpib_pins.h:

#ifndef GPIB_PINS_H_
#define GPIB_PINS_H_

/* GPIB line access for gpib_phy.c, replacing the AVR pin macros.
 * All GPIB lines are 5V-tolerant pins in open-drain mode: ODR=0 drives low, ODR=1 releases. */

#include "stm32f1xx.h"

/* Control lines (open-drain outputs, readable via IDR). Map chosen for a crossing-free layout (docs/hardware.md). */
#define EOI_PORT  GPIOB
#define EOI_PIN   12
#define DAV_PORT  GPIOB
#define DAV_PIN   13
#define NRFD_PORT GPIOB
#define NRFD_PIN  14
#define NDAC_PORT GPIOB
#define NDAC_PIN  15
#define IFC_PORT  GPIOA
#define IFC_PIN   8
#define SRQ_PORT  GPIOA
#define SRQ_PIN   9   /* input only */
#define ATN_PORT  GPIOA
#define ATN_PIN   10
#define REN_PORT  GPIOA
#define REN_PIN   15  /* JTDI: needs JTAG disabled (SWD kept) */

/* DIO1..DIO8 on GPIOB, not in bit order: PB9, PB7, PB10, PB11, PB8, PB6, PB4 (NJTRST), PB3 (JTDO) */
#define DATA_PORT GPIOB
#define DATA_MASK 0x0FD8u

#define LINE_LOW(p, n)   ((p)->BRR  = (1u << (n)))
#define LINE_HIGH(p, n)  ((p)->BSRR = (1u << (n)))
#define LINE_STATE(p, n) ((p)->IDR & (1u << (n)))
#define LINE_OUT(p, n)   ((p)->ODR & (1u << (n)))

#define ATN_LOW   LINE_LOW(ATN_PORT, ATN_PIN)
#define ATN_HIGH  LINE_HIGH(ATN_PORT, ATN_PIN)
#define NDAC_LOW  LINE_LOW(NDAC_PORT, NDAC_PIN)
#define NDAC_HIGH LINE_HIGH(NDAC_PORT, NDAC_PIN)
#define NRFD_LOW  LINE_LOW(NRFD_PORT, NRFD_PIN)
#define NRFD_HIGH LINE_HIGH(NRFD_PORT, NRFD_PIN)
#define DAV_LOW   LINE_LOW(DAV_PORT, DAV_PIN)
#define DAV_HIGH  LINE_HIGH(DAV_PORT, DAV_PIN)
#define EOI_LOW   LINE_LOW(EOI_PORT, EOI_PIN)
#define EOI_HIGH  LINE_HIGH(EOI_PORT, EOI_PIN)
#define REN_LOW   LINE_LOW(REN_PORT, REN_PIN)
#define REN_HIGH  LINE_HIGH(REN_PORT, REN_PIN)
#define IFC_LOW   LINE_LOW(IFC_PORT, IFC_PIN)
#define IFC_HIGH  LINE_HIGH(IFC_PORT, IFC_PIN)

#define DAV_STATE  LINE_STATE(DAV_PORT, DAV_PIN)
#define NDAC_STATE LINE_STATE(NDAC_PORT, NDAC_PIN)
#define NRFD_STATE LINE_STATE(NRFD_PORT, NRFD_PIN)
#define ATN_STATE  LINE_STATE(ATN_PORT, ATN_PIN)
#define EOI_STATE  LINE_STATE(EOI_PORT, EOI_PIN)
#define SRQ_STATE  LINE_STATE(SRQ_PORT, SRQ_PIN)

/* true when ATN is released; replaces the AVR's (DDRF & (1<<6)) == 0 test */
#define ATN_OUT_STATE (LINE_OUT(ATN_PORT, ATN_PIN) != 0)

/* DIO bit i -> PB pin; one IDR read / BSRR write, a few shifts each (cheap at 72 MHz) */
static inline uint32_t data_spread(uint8_t d)
{
	return ((d & 0x01u) << 9) | ((d & 0x02u) << 6) | ((d & 0x04u) << 8) | ((d & 0x08u) << 8) |
	       ((d & 0x10u) << 4) | ((d & 0x20u) << 1) | ((d & 0x40u) >> 2) | ((d & 0x80u) >> 4);
}
static inline uint8_t data_gather(uint32_t r)
{
	return (uint8_t)(((r >> 9) & 0x01u) | ((r >> 6) & 0x02u) | ((r >> 8) & 0x04u) | ((r >> 8) & 0x08u) |
	                 ((r >> 4) & 0x10u) | ((r >> 1) & 0x20u) | ((r << 2) & 0x40u) | ((r << 4) & 0x80u));
}

/* GPIB data is negative logic: a 1 bit pulls the line low. Replaces DDRD = dat / ~PIND. */
#define DATA_WRITE(d) (DATA_PORT->BSRR = (data_spread(d) << 16) | data_spread((uint8_t)~(d)))
#define DATA_RELEASE  (DATA_PORT->BSRR = DATA_MASK)
#define DATA_READ     data_gather(~DATA_PORT->IDR)

/* Replaces the DDR/PORT setup at the top of gpib_init(). Everything starts released; REN keeps its output level
 * (low from reset, as the AVR drives it), phy_init() then sets it. */
static inline void gpib_pins_init(void)
{
	RCC->APB2ENR |= RCC_APB2ENR_AFIOEN | RCC_APB2ENR_IOPAEN | RCC_APB2ENR_IOPBEN;
	AFIO->MAPR = (AFIO->MAPR & ~AFIO_MAPR_SWJ_CFG) | AFIO_MAPR_SWJ_CFG_JTAGDISABLE; /* frees PA15/PB3/PB4 */

	GPIOA->BSRR = (1u << IFC_PIN) | (1u << SRQ_PIN) | (1u << ATN_PIN);
	GPIOB->BSRR = DATA_MASK | (1u << EOI_PIN) | (1u << DAV_PIN) | (1u << NRFD_PIN) | (1u << NDAC_PIN);

	/* 0x7 = open-drain 50MHz, 0x4 = floating input */
	GPIOA->CRH = (GPIOA->CRH & 0x0FFFF000u) | 0x70000747u; /* PA8 OD, PA9 input, PA10 OD, PA15 OD */
	GPIOB->CRL = (GPIOB->CRL & 0x00F00FFFu) | 0x77077000u; /* PB3,4,6,7 OD */
	GPIOB->CRH = 0x77777777u;                              /* PB8..15 */
}

#endif /* GPIB_PINS_H_ */
